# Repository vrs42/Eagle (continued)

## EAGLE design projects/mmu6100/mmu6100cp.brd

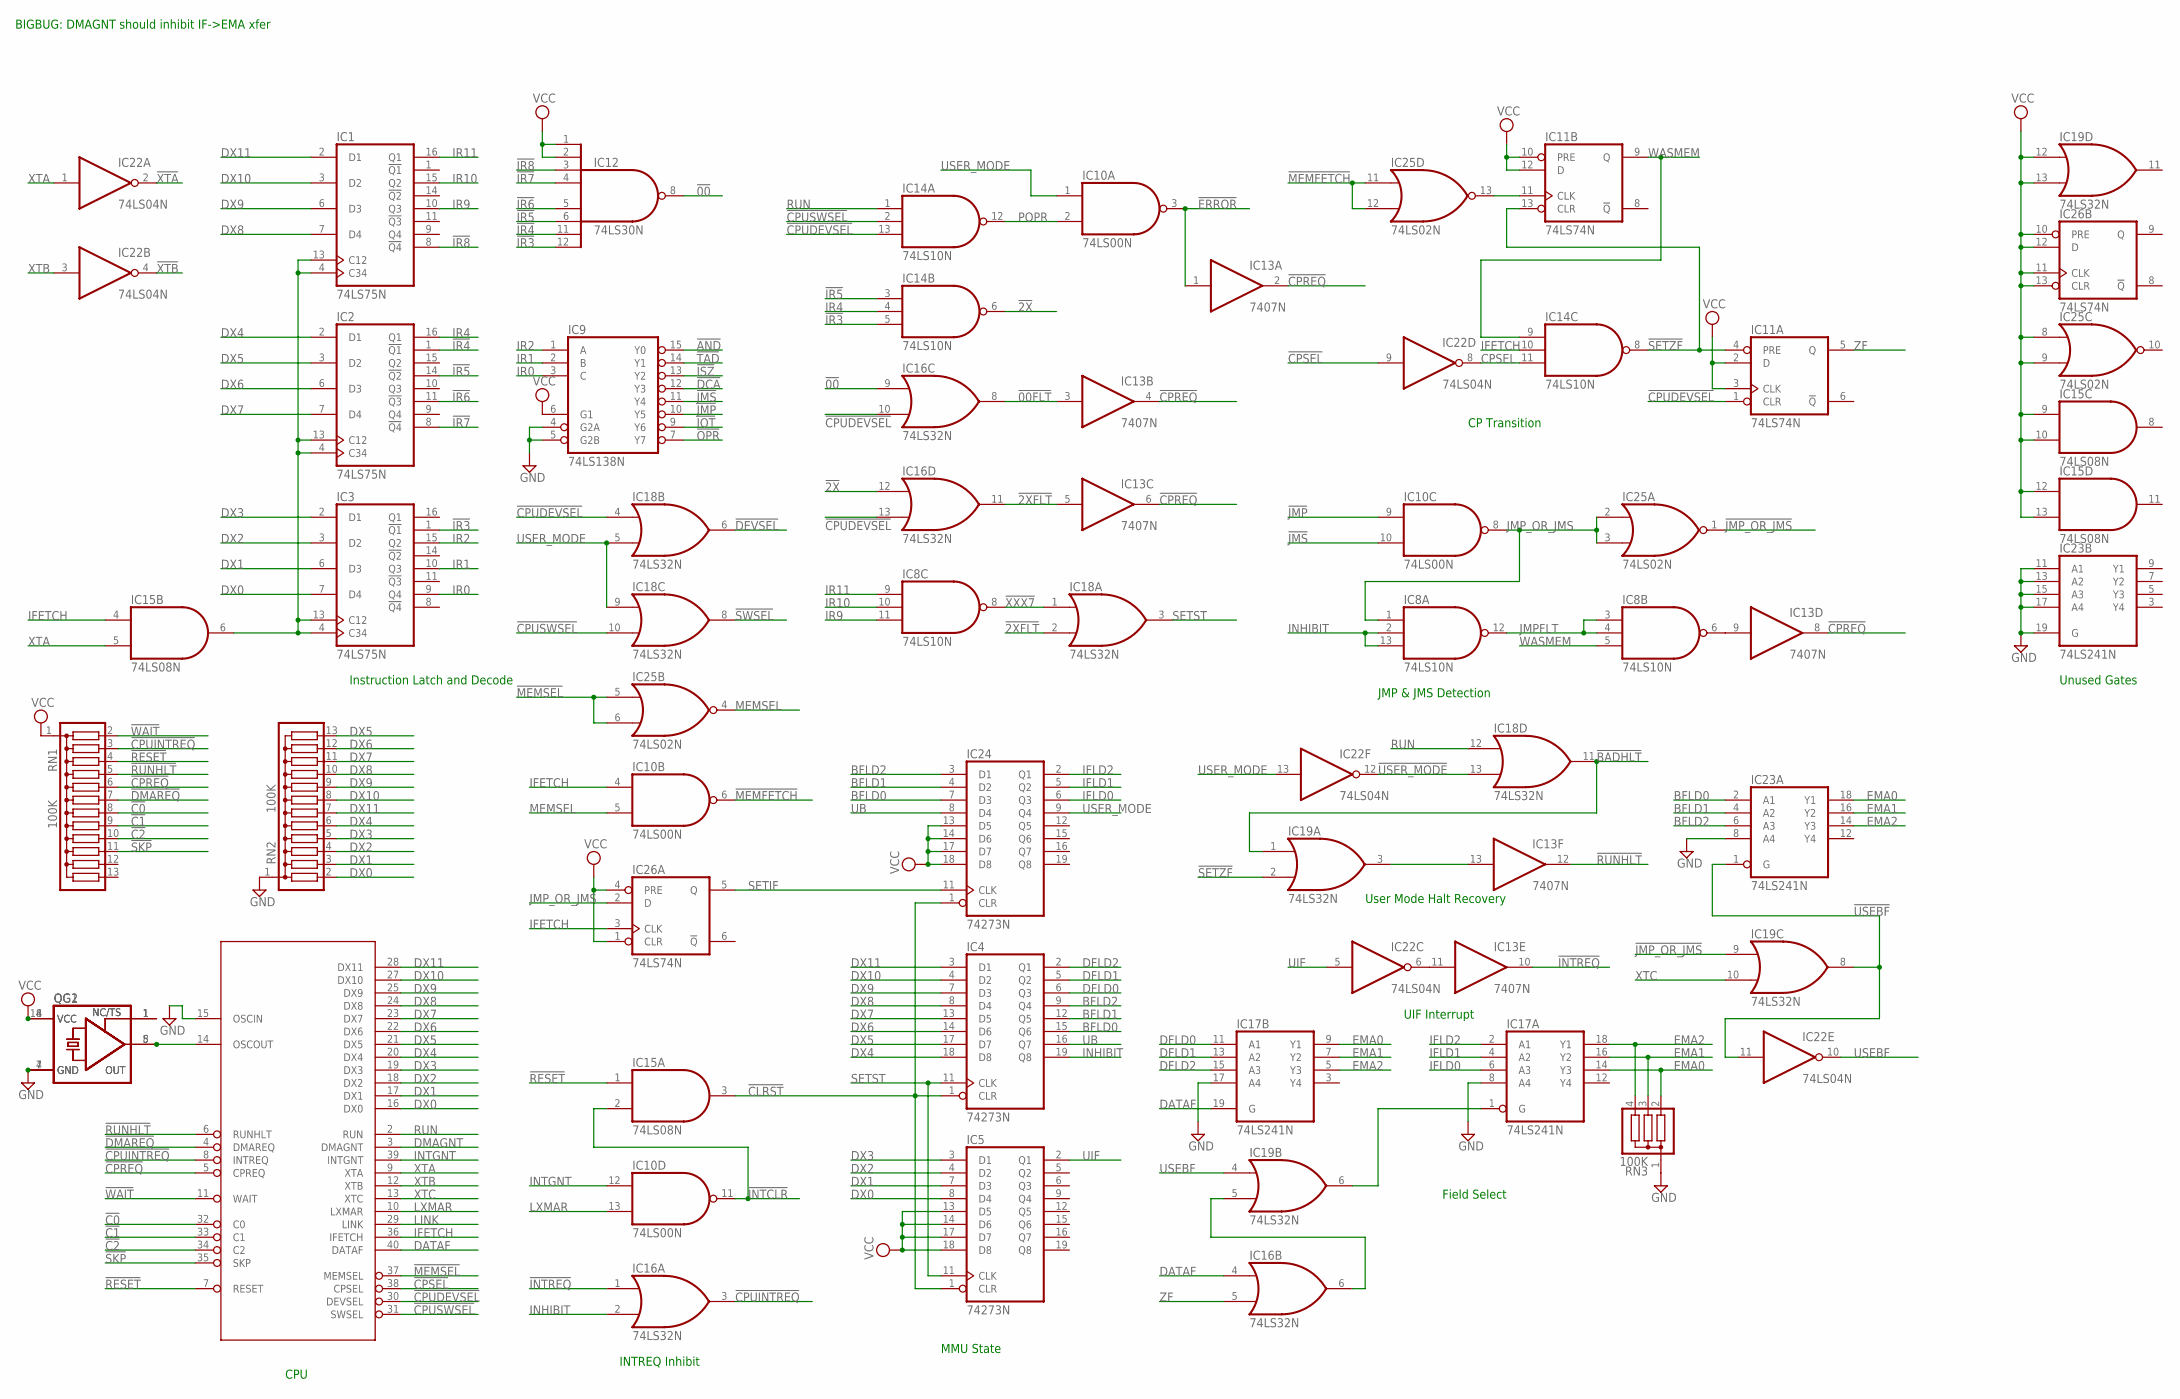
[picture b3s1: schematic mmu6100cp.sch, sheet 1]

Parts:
CPU: IM6100; DIL40
IC1, IC2, IC3: 74LS75N; DIL16
IC4, IC5, IC24: 74273N; DIL20
IC8, IC14: 74LS10N; DIL14
IC9: 74LS138N; DIL16
IC10: 74LS00N; DIL14
IC11, IC26: 74LS74N; DIL14
IC12: 74LS30N; DIL14
IC13: 7407N; DIL14
IC15: 74LS08N; DIL14
IC16, IC18, IC19: 74LS32N; DIL14
IC17, IC23: 74LS241N; DIL20
IC22: 74LS04N; DIL14
IC25: 74LS02N; DIL14
QG1: XO-8; DIL08S
QG2: XO-14; DIL14S
RN1, RN2: 100K; SIL13
RN3: 100K; SIL4

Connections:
!00: IC12.8 (O), IC16.9 (I0)
!00FLT: IC13.3 (I), IC16.8 (O)
!2X: IC14.6 (O), IC16.12 (I0)
!2XFLT: IC13.5 (I), IC16.11 (O), IC18.2 (I1)
!AND: IC9.15 (Y0); also elsewhere on the board
!BADHLT: IC18.11 (O), IC19.1 (I0)
!C0: CPU.32 (C0), RN1.8; also elsewhere on the board
!C1: CPU.33 (C1), RN1.9; also elsewhere on the board
!C2: CPU.34 (C2), RN1.10; also elsewhere on the board
!CLRST: IC4.1 (CLR), IC5.1 (CLR), IC15.3 (O), IC24.1 (CLR)
!CPREQ: CPU.5 (CPREQ), IC13.2 (O), IC13.4 (O), IC13.6 (O), IC13.8 (O), RN1.6; also elsewhere on the board
!CPSEL: CPU.38 (CPSEL), IC22.9 (I)
!CPUDEVSEL: CPU.30 (DEVSEL), IC11.1 (CLR), IC14.13 (I2), IC16.10 (I1), IC16.13 (I1), IC18.4 (I0)
!CPUINTREQ: CPU.8 (INTREQ), IC16.3 (O), RN1.3
!CPUSWSEL: CPU.31 (SWSEL), IC14.2 (I1), IC18.10 (I1)
!DCA: IC9.12 (Y3); also elsewhere on the board
!DEVSEL: IC18.6 (O); also elsewhere on the board
!DMAREQ: CPU.4 (DMAREQ), RN1.7; also elsewhere on the board
!ERROR: IC10.3 (O), IC13.1 (I)
!INTCLR: IC10.11 (O), IC15.2 (I1)
!INTREQ: IC13.10 (O), IC16.1 (I0); also elsewhere on the board
!IOT: IC9.9 (Y6); also elsewhere on the board
!IR3: IC3.1 (!Q1), IC12.12 (I7), IC14.5 (I2)
!IR4: IC2.1 (!Q1), IC12.11 (I6)
!IR5: IC2.14 (!Q2), IC12.6 (I5), IC14.3 (I0)
!IR6: IC2.11 (!Q3), IC12.5 (I4)
!IR7: IC2.8 (!Q4), IC12.4 (I3)
!IR8: IC1.8 (!Q4), IC12.3 (I2)
!ISZ: IC9.13 (Y2); also elsewhere on the board
!JMP: IC9.10 (Y5), IC10.9 (I0)
!JMP_OR_JMS: IC19.9 (I0), IC25.1 (O)
!JMS: IC9.11 (Y4), IC10.10 (I1)
!MEMFETCH: IC10.6 (O), IC25.11 (I0), IC25.12 (I1)
!MEMSEL: CPU.37 (MEMSEL), IC25.5 (I0), IC25.6 (I1); also elsewhere on the board
!OPR: IC9.7 (Y7); also elsewhere on the board
!RESET: CPU.7 (RESET), IC15.1 (I0), RN1.4; also elsewhere on the board
!RUNHLT: CPU.6 (RUNHLT), IC13.12 (O), RN1.5; also elsewhere on the board
!SETZF: IC11.4 (PRE), IC11.13 (CLR), IC14.8 (O), IC19.2 (I1)
!SKP: CPU.35 (SKP), RN1.11; also elsewhere on the board
!SWSEL: IC18.8 (O); also elsewhere on the board
!TAD: IC9.14 (Y1); also elsewhere on the board
!USEBF: IC19.8 (O), IC22.11 (I), IC23.1 (G)
!USER_MODE: IC18.13 (I1), IC22.12 (O)
!WAIT: CPU.11 (WAIT), RN1.2; also elsewhere on the board
!XTA: IC22.2 (O)
!XTB: IC22.4 (O)
!XXX7: IC8.8 (O), IC18.1 (I0)
BFLD0: IC4.15 (Q6), IC23.2 (A1), IC24.7 (D3)
BFLD1: IC4.12 (Q5), IC23.4 (A2), IC24.4 (D2)
BFLD2: IC4.9 (Q4), IC23.6 (A3), IC24.3 (D1)
CPSEL: IC14.11 (I2), IC22.8 (O); also elsewhere on the board
DATAF: CPU.40 (DATAF), IC16.4 (I0), IC17.19 (G)
DFLD0: IC4.6 (Q3), IC17.11 (A1)
DFLD1: IC4.5 (Q2), IC17.13 (A2)
DFLD2: IC4.2 (Q1), IC17.15 (A3)
DMAGNT: CPU.3 (DMAGNT); also elsewhere on the board
DX0: CPU.16 (DX0), IC3.7 (D4), IC5.8 (D4), RN2.2; also elsewhere on the board
DX1: CPU.17 (DX1), IC3.6 (D3), IC5.7 (D3), RN2.3; also elsewhere on the board
DX2: CPU.18 (DX2), IC3.3 (D2), IC5.4 (D2), RN2.4; also elsewhere on the board
DX3: CPU.19 (DX3), IC3.2 (D1), IC5.3 (D1), RN2.5; also elsewhere on the board
DX4: CPU.20 (DX4), IC2.2 (D1), IC4.18 (D8), RN2.6; also elsewhere on the board
DX5: CPU.21 (DX5), IC2.3 (D2), IC4.17 (D7), RN2.13; also elsewhere on the board
DX6: CPU.22 (DX6), IC2.6 (D3), IC4.14 (D6), RN2.12; also elsewhere on the board
DX7: CPU.23 (DX7), IC2.7 (D4), IC4.13 (D5), RN2.11; also elsewhere on the board
DX8: CPU.24 (DX8), IC1.7 (D4), IC4.8 (D4), RN2.10; also elsewhere on the board
DX9: CPU.25 (DX9), IC1.6 (D3), IC4.7 (D3), RN2.9; also elsewhere on the board
DX10: CPU.27 (DX10), IC1.3 (D2), IC4.4 (D2), RN2.8; also elsewhere on the board
DX11: CPU.28 (DX11), IC1.2 (D1), IC4.3 (D1), RN2.7; also elsewhere on the board
EMA0: IC17.9 (Y1), IC17.14 (Y3), IC23.18 (Y1), RN3.2; also elsewhere on the board
EMA1: IC17.7 (Y2), IC17.16 (Y2), IC23.16 (Y2), RN3.3; also elsewhere on the board
EMA2: IC17.5 (Y3), IC17.18 (Y1), IC23.14 (Y3), RN3.4; also elsewhere on the board
GND: CPU.15 (OSCIN), CPU.26 (GND), IC1.12 (GND), IC2.12 (GND), IC3.12 (GND), IC4.10 (GND), IC5.10 (GND), IC8.7 (GND), IC9.4 (G2A), IC9.5 (G2B), IC9.8 (GND), IC10.7 (GND), IC11.7 (GND), IC12.7 (GND), IC13.7 (GND), IC14.7 (GND), IC15.7 (GND), IC16.7 (GND), IC17.8 (A4), IC17.10 (GND), IC17.17 (A4), IC18.7 (GND), IC19.7 (GND), IC22.7 (GND), IC23.8 (A4), IC23.10 (GND), IC23.11 (A1), IC23.13 (A2), IC23.15 (A3), IC23.17 (A4), IC23.19 (G), IC24.10 (GND), IC25.7 (GND), IC26.7 (GND), QG1.4 (GND), QG2.7 (GND), RN2.1, RN3.1; also elsewhere on the board
IFETCH: CPU.36 (IFETCH), IC10.4 (I0), IC14.10 (I1), IC15.4 (I0), IC26.3 (CLK)
IFLD0: IC17.6 (A3), IC24.6 (Q3)
IFLD1: IC17.4 (A2), IC24.5 (Q2)
IFLD2: IC17.2 (A1), IC24.2 (Q1)
INHIBIT: IC4.19 (Q8), IC8.2 (I1), IC8.13 (I2), IC16.2 (I1)
INTGNT: CPU.39 (INTGNT), IC10.12 (I0); also elsewhere on the board
IR0: IC3.9 (Q4), IC9.3 (C)
IR1: IC3.10 (Q3), IC9.2 (B)
IR2: IC3.15 (Q2), IC9.1 (A)
IR4: IC2.16 (Q1), IC14.4 (I1)
IR9: IC1.10 (Q3), IC8.11 (I2)
IR10: IC1.15 (Q2), IC8.10 (I1)
IR11: IC1.16 (Q1), IC8.9 (I0)
JMPFLT: IC8.3 (I0), IC8.4 (I1), IC8.12 (O)
JMP_OR_JMS: IC8.1 (I0), IC10.8 (O), IC25.2 (I0), IC25.3 (I1), IC26.2 (D)
LINK: CPU.29 (LINK); also elsewhere on the board
LXMAR: CPU.10 (LXMAR), IC10.13 (I1); also elsewhere on the board
MEMSEL: IC10.5 (I1), IC25.4 (O); also elsewhere on the board
unnamed: QG1.1 (TS), QG2.1 (TS)
unnamed: IC1.4 (C34), IC1.13 (C12), IC2.4 (C34), IC2.13 (C12), IC3.4 (C34), IC3.13 (C12), IC15.6 (O)
unnamed: IC13.11 (I), IC22.6 (O)
unnamed: IC11.11 (CLK), IC25.13 (O)
unnamed: IC13.13 (I), IC19.3 (O)
unnamed: IC16.6 (O), IC19.5 (I1)
unnamed: IC17.1 (G), IC19.6 (O)
unnamed: IC8.6 (O), IC13.9 (I)
OSCOUT: CPU.14 (OSCOUT), QG1.5 (OUT), QG2.8 (OUT)
POPR: IC10.2 (I1), IC14.12 (O)
RUN: CPU.2 (RUN), IC14.1 (I0), IC18.12 (I0)
SETIF: IC24.11 (CLK), IC26.5 (Q)
SETST: IC4.11 (CLK), IC5.11 (CLK), IC18.3 (O)
UB: IC4.16 (Q7), IC24.8 (D4)
UIF: IC5.2 (Q1), IC22.5 (I)
USEBF: IC19.4 (I0), IC22.10 (O)
USER_MODE: IC10.1 (I0), IC18.5 (I1), IC18.9 (I0), IC22.13 (I), IC24.9 (Q4)
VCC: CPU.1 (VCC), IC1.5 (VCC), IC2.5 (VCC), IC3.5 (VCC), IC4.20 (VCC), IC5.13 (D5), IC5.14 (D6), IC5.17 (D7), IC5.18 (D8), IC5.20 (VCC), IC8.14 (VCC), IC9.6 (G1), IC9.16 (VCC), IC10.14 (VCC), IC11.2 (D), IC11.3 (CLK), IC11.10 (PRE), IC11.12 (D), IC11.14 (VCC), IC12.1 (I0), IC12.2 (I1), IC12.14 (VCC), IC13.14 (VCC), IC14.14 (VCC), IC15.9 (I0), IC15.10 (I1), IC15.12 (I0), IC15.13 (I1), IC15.14 (VCC), IC16.14 (VCC), IC17.20 (VCC), IC18.14 (VCC), IC19.12 (I0), IC19.13 (I1), IC19.14 (VCC), IC22.14 (VCC), IC23.20 (VCC), IC24.13 (D5), IC24.14 (D6), IC24.17 (D7), IC24.18 (D8), IC24.20 (VCC), IC25.8 (I0), IC25.9 (I1), IC25.14 (VCC), IC26.1 (CLR), IC26.4 (PRE), IC26.10 (PRE), IC26.11 (CLK), IC26.12 (D), IC26.13 (CLR), IC26.14 (VCC), QG1.8 (VCC), QG2.14 (VCC), RN1.1; also elsewhere on the board
WASMEM: IC8.5 (I2), IC11.9 (Q), IC14.9 (I0)
XTA: CPU.9 (XTA), IC15.5 (I1), IC22.1 (I); also elsewhere on the board
XTB: CPU.12 (XTB), IC22.3 (I); also elsewhere on the board
XTC: CPU.13 (XTC), IC19.10 (I1); also elsewhere on the board
ZF: IC11.5 (Q), IC16.5 (I1)

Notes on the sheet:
Instruction Latch and Decode
CPU
Field Select
INTREQ Inhibit
JMP & JMS Detection
CP Transition
MMU State
Unused Gates
User Mode Halt Recovery
UIF Interrupt
BIGBUG: DMAGNT should inhibit IF->EMA xfer

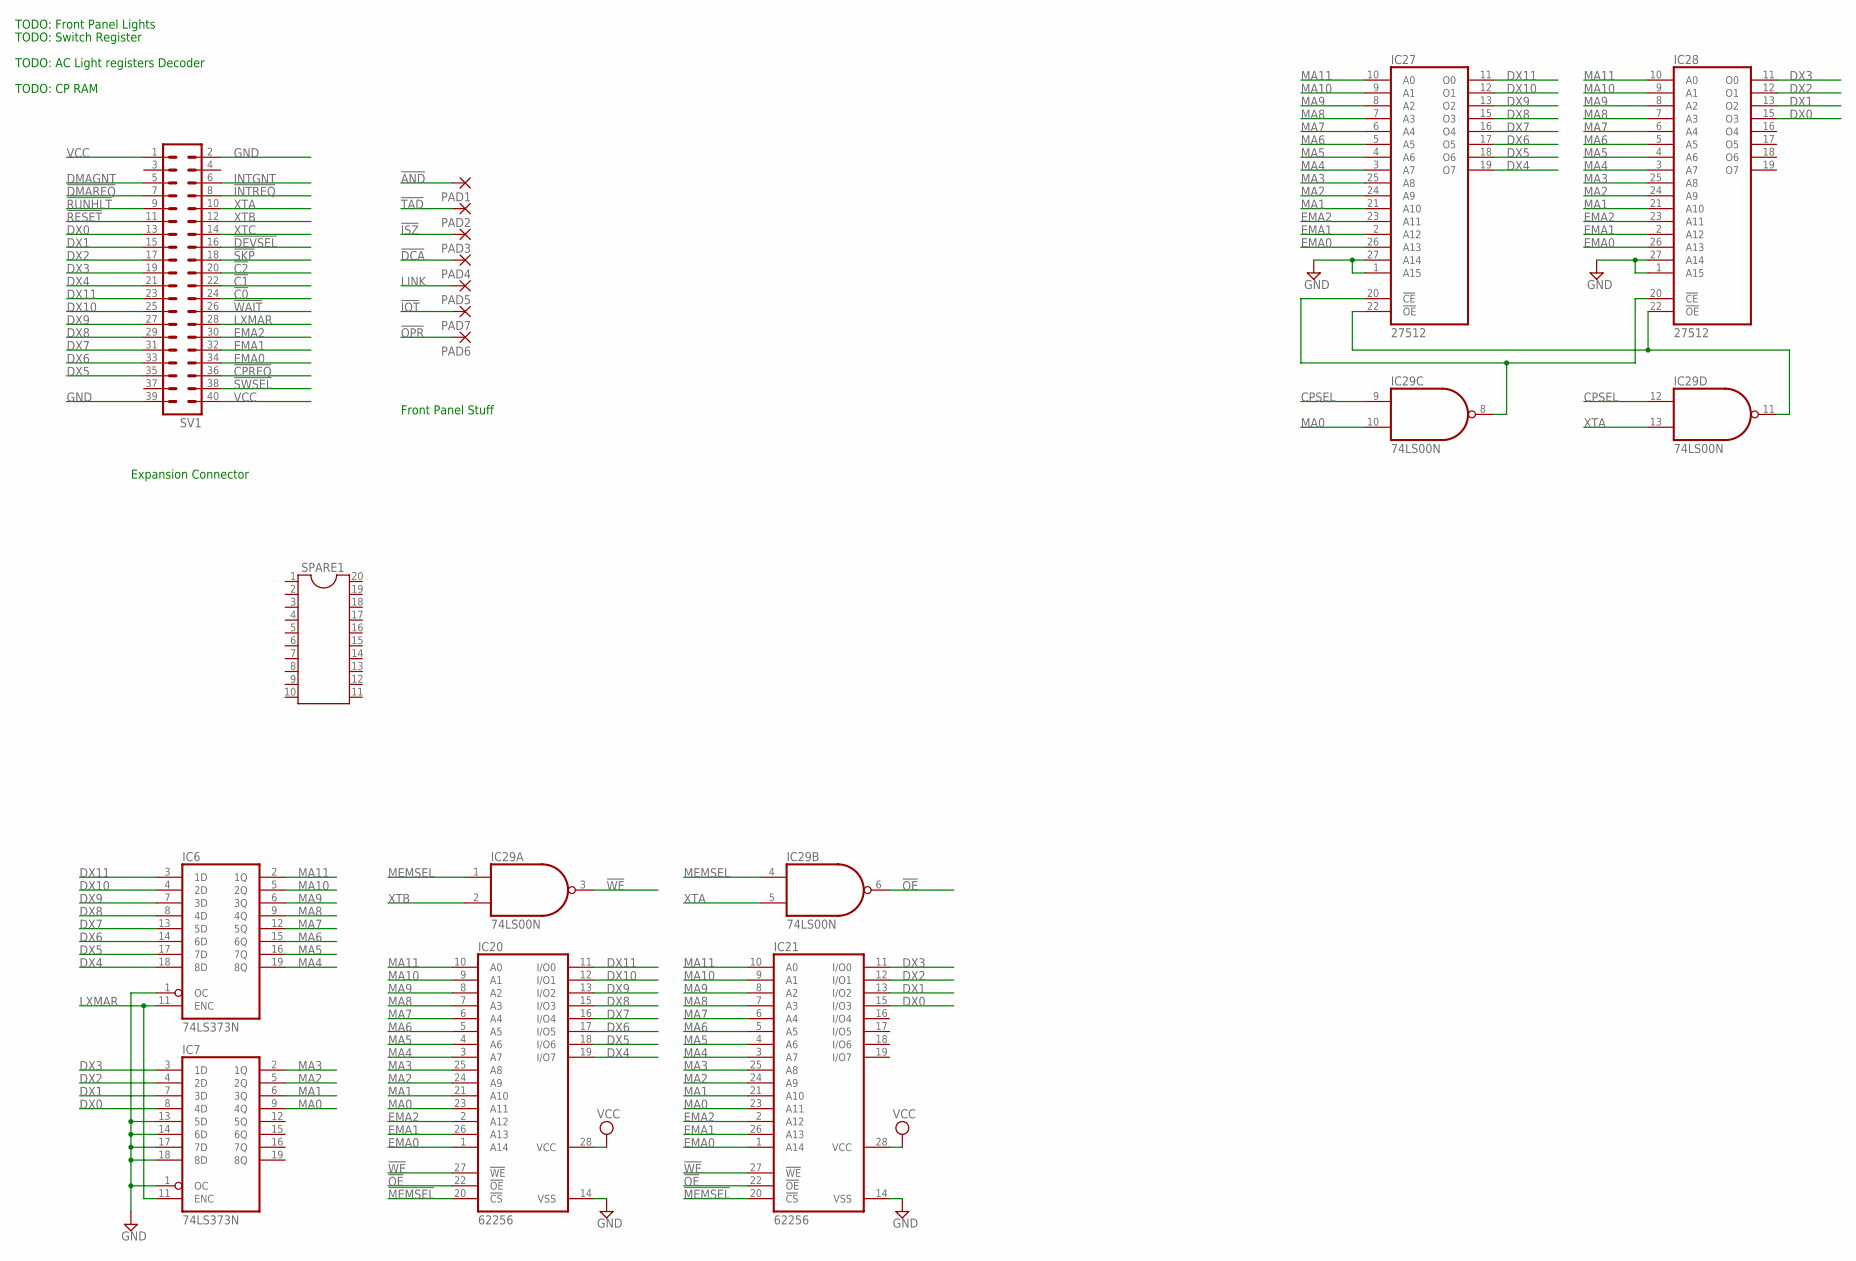
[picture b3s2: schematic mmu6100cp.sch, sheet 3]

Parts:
IC6, IC7: 74LS373N; DIL20
IC20, IC21: 62256; DIL28-6
IC27, IC28: 27512; DIL28
IC29: 74LS00N; DIL14
PAD1, PAD2, PAD3, PAD4, PAD5, PAD6, PAD7: 2,15/1,0
SPARE1: DIL20
SV1: MA20-2

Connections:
!AND: PAD1.1; also elsewhere on the board
!C0: SV1.24; also elsewhere on the board
!C1: SV1.22; also elsewhere on the board
!C2: SV1.20; also elsewhere on the board
!CPREQ: SV1.36; also elsewhere on the board
!DCA: PAD4.1; also elsewhere on the board
!DEVSEL: SV1.16; also elsewhere on the board
!DMAREQ: SV1.7; also elsewhere on the board
!INTREQ: SV1.8; also elsewhere on the board
!IOT: PAD7.1; also elsewhere on the board
!ISZ: PAD3.1; also elsewhere on the board
!MEMSEL: IC20.20 (!CS), IC21.20 (!CS); also elsewhere on the board
!OE: IC20.22 (!OE), IC21.22 (!OE), IC29.6 (O)
!OPR: PAD6.1; also elsewhere on the board
!RESET: SV1.11; also elsewhere on the board
!RUNHLT: SV1.9; also elsewhere on the board
!SKP: SV1.18; also elsewhere on the board
!SWSEL: SV1.38; also elsewhere on the board
!TAD: PAD2.1; also elsewhere on the board
!WAIT: SV1.26; also elsewhere on the board
!WE: IC20.27 (!WE), IC21.27 (!WE), IC29.3 (O)
CPSEL: IC29.9 (I0), IC29.12 (I0); also elsewhere on the board
DMAGNT: SV1.5; also elsewhere on the board
DX0: IC7.8 (4D), IC21.15 (I/O3), IC28.15 (O3), SV1.13; also elsewhere on the board
DX1: IC7.7 (3D), IC21.13 (I/O2), IC28.13 (O2), SV1.15; also elsewhere on the board
DX2: IC7.4 (2D), IC21.12 (I/O1), IC28.12 (O1), SV1.17; also elsewhere on the board
DX3: IC7.3 (1D), IC21.11 (I/O0), IC28.11 (O0), SV1.19; also elsewhere on the board
DX4: IC6.18 (8D), IC20.19 (I/O7), IC27.19 (O7), SV1.21; also elsewhere on the board
DX5: IC6.17 (7D), IC20.18 (I/O6), IC27.18 (O6), SV1.35; also elsewhere on the board
DX6: IC6.14 (6D), IC20.17 (I/O5), IC27.17 (O5), SV1.33; also elsewhere on the board
DX7: IC6.13 (5D), IC20.16 (I/O4), IC27.16 (O4), SV1.31; also elsewhere on the board
DX8: IC6.8 (4D), IC20.15 (I/O3), IC27.15 (O3), SV1.29; also elsewhere on the board
DX9: IC6.7 (3D), IC20.13 (I/O2), IC27.13 (O2), SV1.27; also elsewhere on the board
DX10: IC6.4 (2D), IC20.12 (I/O1), IC27.12 (O1), SV1.25; also elsewhere on the board
DX11: IC6.3 (1D), IC20.11 (I/O0), IC27.11 (O0), SV1.23; also elsewhere on the board
EMA0: IC20.1 (A14), IC21.1 (A14), IC27.26 (A13), IC28.26 (A13), SV1.34; also elsewhere on the board
EMA1: IC20.26 (A13), IC21.26 (A13), IC27.2 (A12), IC28.2 (A12), SV1.32; also elsewhere on the board
EMA2: IC20.2 (A12), IC21.2 (A12), IC27.23 (A11), IC28.23 (A11), SV1.30; also elsewhere on the board
GND: IC6.1 (OC), IC6.10 (GND), IC7.1 (OC), IC7.10 (GND), IC7.13 (5D), IC7.14 (6D), IC7.17 (7D), IC7.18 (8D), IC20.14 (VSS), IC21.14 (VSS), IC27.1 (A15), IC27.14 (GND), IC27.27 (A14), IC28.1 (A15), IC28.14 (GND), IC28.27 (A14), IC29.7 (GND), SV1.2, SV1.39; also elsewhere on the board
INTGNT: SV1.6; also elsewhere on the board
LINK: PAD5.1; also elsewhere on the board
LXMAR: IC6.11 (ENC), IC7.11 (ENC), SV1.28; also elsewhere on the board
MA0: IC7.9 (4Q), IC20.23 (A11), IC21.23 (A11), IC29.10 (I1)
MA1: IC7.6 (3Q), IC20.21 (A10), IC21.21 (A10), IC27.21 (A10), IC28.21 (A10)
MA2: IC7.5 (2Q), IC20.24 (A9), IC21.24 (A9), IC27.24 (A9), IC28.24 (A9)
MA3: IC7.2 (1Q), IC20.25 (A8), IC21.25 (A8), IC27.25 (A8), IC28.25 (A8)
MA4: IC6.19 (8Q), IC20.3 (A7), IC21.3 (A7), IC27.3 (A7), IC28.3 (A7)
MA5: IC6.16 (7Q), IC20.4 (A6), IC21.4 (A6), IC27.4 (A6), IC28.4 (A6)
MA6: IC6.15 (6Q), IC20.5 (A5), IC21.5 (A5), IC27.5 (A5), IC28.5 (A5)
MA7: IC6.12 (5Q), IC20.6 (A4), IC21.6 (A4), IC27.6 (A4), IC28.6 (A4)
MA8: IC6.9 (4Q), IC20.7 (A3), IC21.7 (A3), IC27.7 (A3), IC28.7 (A3)
MA9: IC6.6 (3Q), IC20.8 (A2), IC21.8 (A2), IC27.8 (A2), IC28.8 (A2)
MA10: IC6.5 (2Q), IC20.9 (A1), IC21.9 (A1), IC27.9 (A1), IC28.9 (A1)
MA11: IC6.2 (1Q), IC20.10 (A0), IC21.10 (A0), IC27.10 (A0), IC28.10 (A0)
MEMSEL: IC29.1 (I0), IC29.4 (I0); also elsewhere on the board
unnamed: IC27.20 (!CE), IC28.20 (!CE), IC29.8 (O)
unnamed: IC27.22 (!OE), IC28.22 (!OE), IC29.11 (O)
VCC: IC6.20 (VCC), IC7.20 (VCC), IC20.28 (VCC), IC21.28 (VCC), IC27.28 (VCC), IC28.28 (VCC), IC29.14 (VCC), SV1.1, SV1.40; also elsewhere on the board
XTA: IC29.5 (I1), IC29.13 (I1), SV1.10; also elsewhere on the board
XTB: IC29.2 (I1), SV1.12; also elsewhere on the board
XTC: SV1.14; also elsewhere on the board

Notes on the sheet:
Expansion Connector
Front Panel Stuff
TODO: Front Panel Lights
TODO: Switch Register
TODO: AC Light registers Decoder
TODO: CP RAM

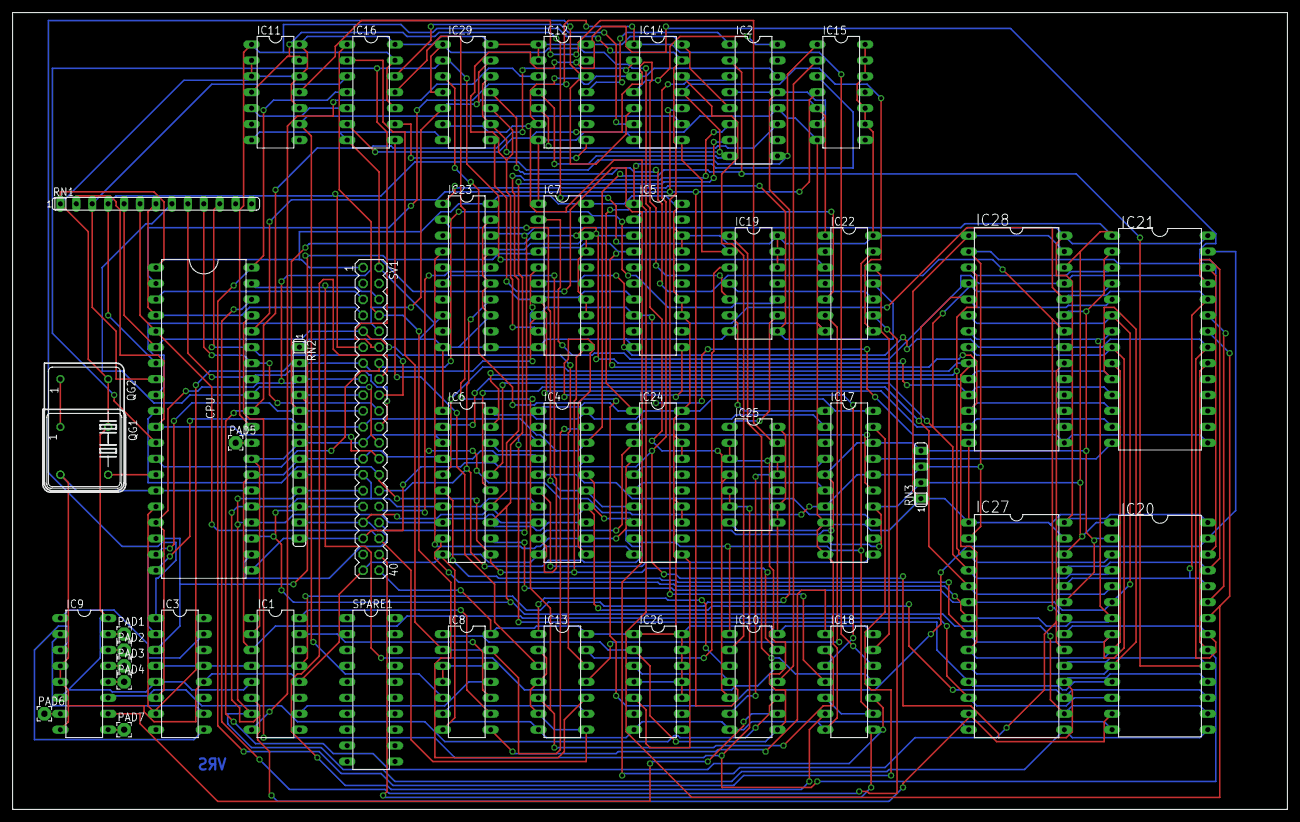
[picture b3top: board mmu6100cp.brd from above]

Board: 2 copper layers, 203.2 x 127.0 mm, 44 parts (0 on the bottom side), 127 nets.

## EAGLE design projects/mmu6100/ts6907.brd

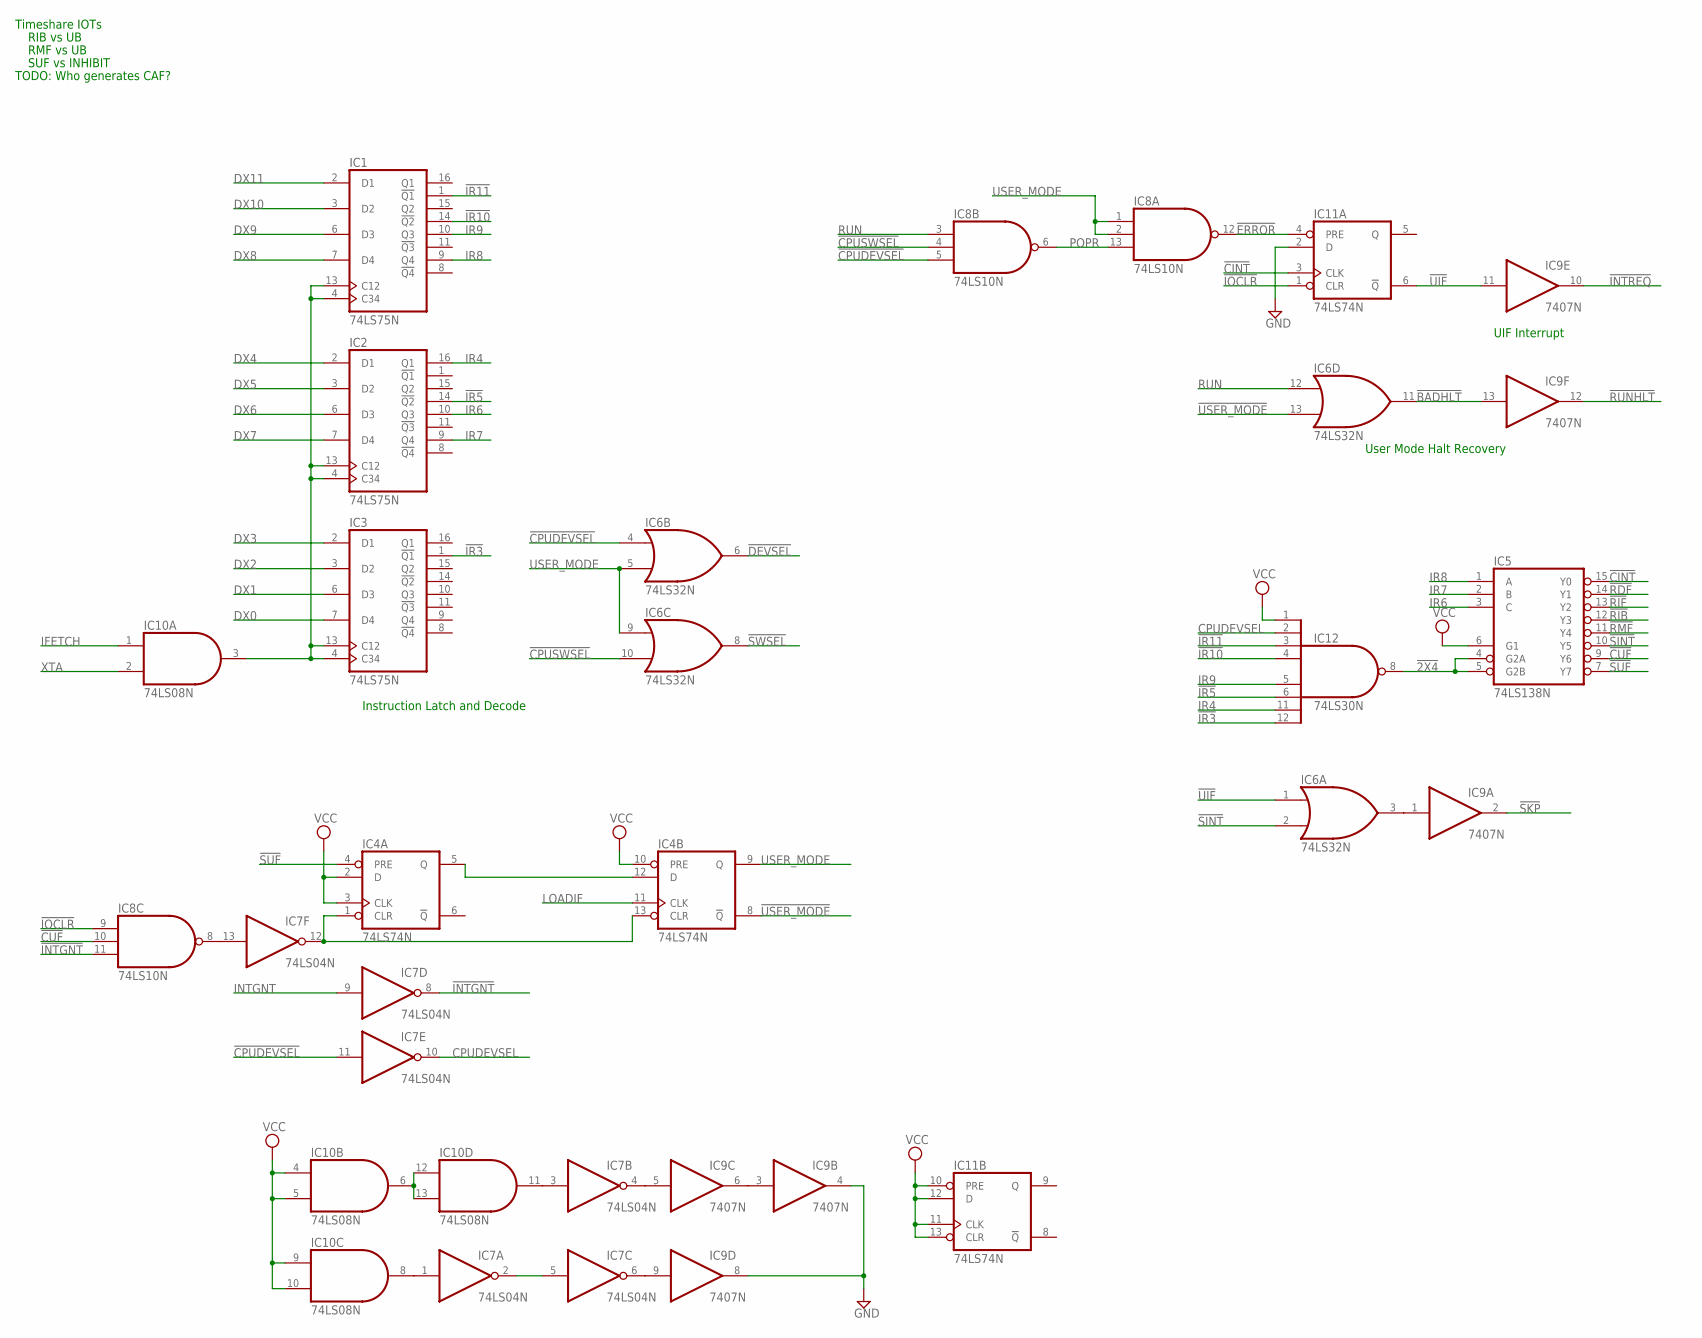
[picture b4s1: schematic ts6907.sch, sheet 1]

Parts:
IC1, IC2, IC3: 74LS75N; DIL16
IC4, IC11: 74LS74N; DIL14
IC5: 74LS138N; DIL16
IC6: 74LS32N; DIL14
IC7: 74LS04N; DIL14
IC8: 74LS10N; DIL14
IC9: 7407N; DIL14
IC10: 74LS08N; DIL14
IC12: 74LS30N; DIL14

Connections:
!2X4: IC5.4 (G2A), IC5.5 (G2B), IC12.8 (O)
!BADHLT: IC6.11 (O), IC9.13 (I)
!CINT: IC5.15 (Y0), IC11.3 (CLK)
!CPUDEVSEL: IC6.4 (I0), IC7.11 (I), IC8.5 (I2); also elsewhere on the board
!CPUSWSEL: IC6.10 (I1), IC8.4 (I1); also elsewhere on the board
!CUF: IC5.9 (Y6), IC8.10 (I1)
!DEVSEL: IC6.6 (O); also elsewhere on the board
!ERROR: IC8.12 (O), IC11.4 (PRE)
!INTGNT: IC7.8 (O), IC8.11 (I2)
!INTREQ: IC9.10 (O); also elsewhere on the board
!IOCLR: IC8.9 (I0), IC11.1 (CLR); also elsewhere on the board
!IR3: IC3.1 (!Q1), IC12.12 (I7)
!IR5: IC2.14 (!Q2), IC12.6 (I5)
!IR10: IC1.14 (!Q2), IC12.4 (I3)
!IR11: IC1.1 (!Q1), IC12.3 (I2)
!RDF: IC5.14 (Y1)
!RIB: IC5.12 (Y3)
!RIF: IC5.13 (Y2)
!RMF: IC5.11 (Y4)
!RUNHLT: IC9.12 (O); also elsewhere on the board
!SINT: IC5.10 (Y5), IC6.2 (I1)
!SKP: IC9.2 (O); also elsewhere on the board
!SUF: IC4.4 (PRE), IC5.7 (Y7)
!SWSEL: IC6.8 (O); also elsewhere on the board
!UIF: IC6.1 (I0), IC9.11 (I), IC11.6 (!Q)
!USER_MODE: IC4.8 (!Q), IC6.13 (I1)
CPUDEVSEL: IC7.10 (O), IC12.2 (I1)
DX0: IC3.7 (D4); also elsewhere on the board
DX1: IC3.6 (D3); also elsewhere on the board
DX2: IC3.3 (D2); also elsewhere on the board
DX3: IC3.2 (D1); also elsewhere on the board
DX4: IC2.2 (D1); also elsewhere on the board
DX5: IC2.3 (D2); also elsewhere on the board
DX6: IC2.6 (D3); also elsewhere on the board
DX7: IC2.7 (D4); also elsewhere on the board
DX8: IC1.7 (D4); also elsewhere on the board
DX9: IC1.6 (D3); also elsewhere on the board
DX10: IC1.3 (D2); also elsewhere on the board
DX11: IC1.2 (D1); also elsewhere on the board
GND: IC1.12 (GND), IC2.12 (GND), IC3.12 (GND), IC4.7 (GND), IC5.8 (GND), IC6.7 (GND), IC7.7 (GND), IC8.7 (GND), IC9.4 (O), IC9.7 (GND), IC9.8 (O), IC10.7 (GND), IC11.2 (D), IC11.7 (GND), IC12.7 (GND); also elsewhere on the board
IFETCH: IC10.1 (I0); also elsewhere on the board
INTGNT: IC7.9 (I); also elsewhere on the board
IR4: IC2.16 (Q1), IC12.11 (I6)
IR6: IC2.10 (Q3), IC5.3 (C)
IR7: IC2.9 (Q4), IC5.2 (B)
IR8: IC1.9 (Q4), IC5.1 (A)
IR9: IC1.10 (Q3), IC12.5 (I4)
LOADIF: IC4.11 (CLK); also elsewhere on the board
unnamed: IC4.5 (Q), IC4.12 (D)
unnamed: IC7.1 (I), IC10.8 (O)
unnamed: IC1.4 (C34), IC1.13 (C12), IC2.4 (C34), IC2.13 (C12), IC3.4 (C34), IC3.13 (C12), IC10.3 (O)
unnamed: IC4.1 (CLR), IC4.13 (CLR), IC7.12 (O)
unnamed: IC7.3 (I), IC10.11 (O)
unnamed: IC7.2 (O), IC7.5 (I)
unnamed: IC10.6 (O), IC10.12 (I0), IC10.13 (I1)
unnamed: IC7.4 (O), IC9.5 (I)
unnamed: IC7.6 (O), IC9.9 (I)
unnamed: IC9.3 (I), IC9.6 (O)
unnamed: IC6.3 (O), IC9.1 (I)
unnamed: IC7.13 (I), IC8.8 (O)
POPR: IC8.6 (O), IC8.13 (I2)
RUN: IC6.12 (I0), IC8.3 (I0); also elsewhere on the board
USER_MODE: IC4.9 (Q), IC6.5 (I1), IC6.9 (I0), IC8.1 (I0), IC8.2 (I1)
VCC: IC1.5 (VCC), IC2.5 (VCC), IC3.5 (VCC), IC4.2 (D), IC4.3 (CLK), IC4.10 (PRE), IC4.14 (VCC), IC5.6 (G1), IC5.16 (VCC), IC6.14 (VCC), IC7.14 (VCC), IC8.14 (VCC), IC9.14 (VCC), IC10.4 (I0), IC10.5 (I1), IC10.9 (I0), IC10.10 (I1), IC10.14 (VCC), IC11.10 (PRE), IC11.11 (CLK), IC11.12 (D), IC11.13 (CLR), IC11.14 (VCC), IC12.1 (I0), IC12.14 (VCC); also elsewhere on the board
XTA: IC10.2 (I1); also elsewhere on the board

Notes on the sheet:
Instruction Latch and Decode
User Mode Halt Recovery
UIF Interrupt
TODO: Who generates CAF?
Timeshare IOTs
RIB vs UB
RMF vs UB
SUF vs INHIBIT

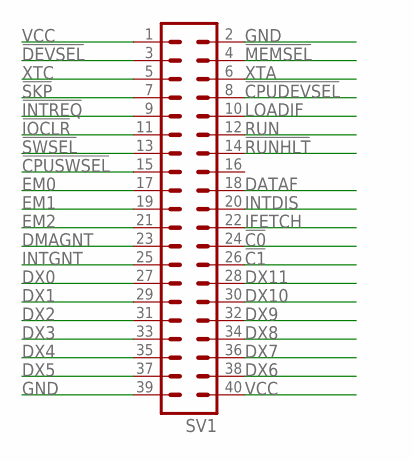
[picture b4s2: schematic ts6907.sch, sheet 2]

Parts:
SV1: MA20-2

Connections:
!C0: SV1.24
!C1: SV1.26
!CPUDEVSEL: SV1.8; also elsewhere on the board
!CPUSWSEL: SV1.15; also elsewhere on the board
!DEVSEL: SV1.3; also elsewhere on the board
!INTREQ: SV1.9; also elsewhere on the board
!IOCLR: SV1.11; also elsewhere on the board
!MEMSEL: SV1.4
!RUNHLT: SV1.14; also elsewhere on the board
!SKP: SV1.7; also elsewhere on the board
!SWSEL: SV1.13; also elsewhere on the board
DATAF: SV1.18
DMAGNT: SV1.23
DX0: SV1.27; also elsewhere on the board
DX1: SV1.29; also elsewhere on the board
DX2: SV1.31; also elsewhere on the board
DX3: SV1.33; also elsewhere on the board
DX4: SV1.35; also elsewhere on the board
DX5: SV1.37; also elsewhere on the board
DX6: SV1.38; also elsewhere on the board
DX7: SV1.36; also elsewhere on the board
DX8: SV1.34; also elsewhere on the board
DX9: SV1.32; also elsewhere on the board
DX10: SV1.30; also elsewhere on the board
DX11: SV1.28; also elsewhere on the board
EM0: SV1.17
EM1: SV1.19
EM2: SV1.21
GND: SV1.2, SV1.39; also elsewhere on the board
IFETCH: SV1.22; also elsewhere on the board
INTDIS: SV1.20
INTGNT: SV1.25; also elsewhere on the board
LOADIF: SV1.10; also elsewhere on the board
RUN: SV1.12; also elsewhere on the board
VCC: SV1.1, SV1.40; also elsewhere on the board
XTA: SV1.6; also elsewhere on the board
XTC: SV1.5

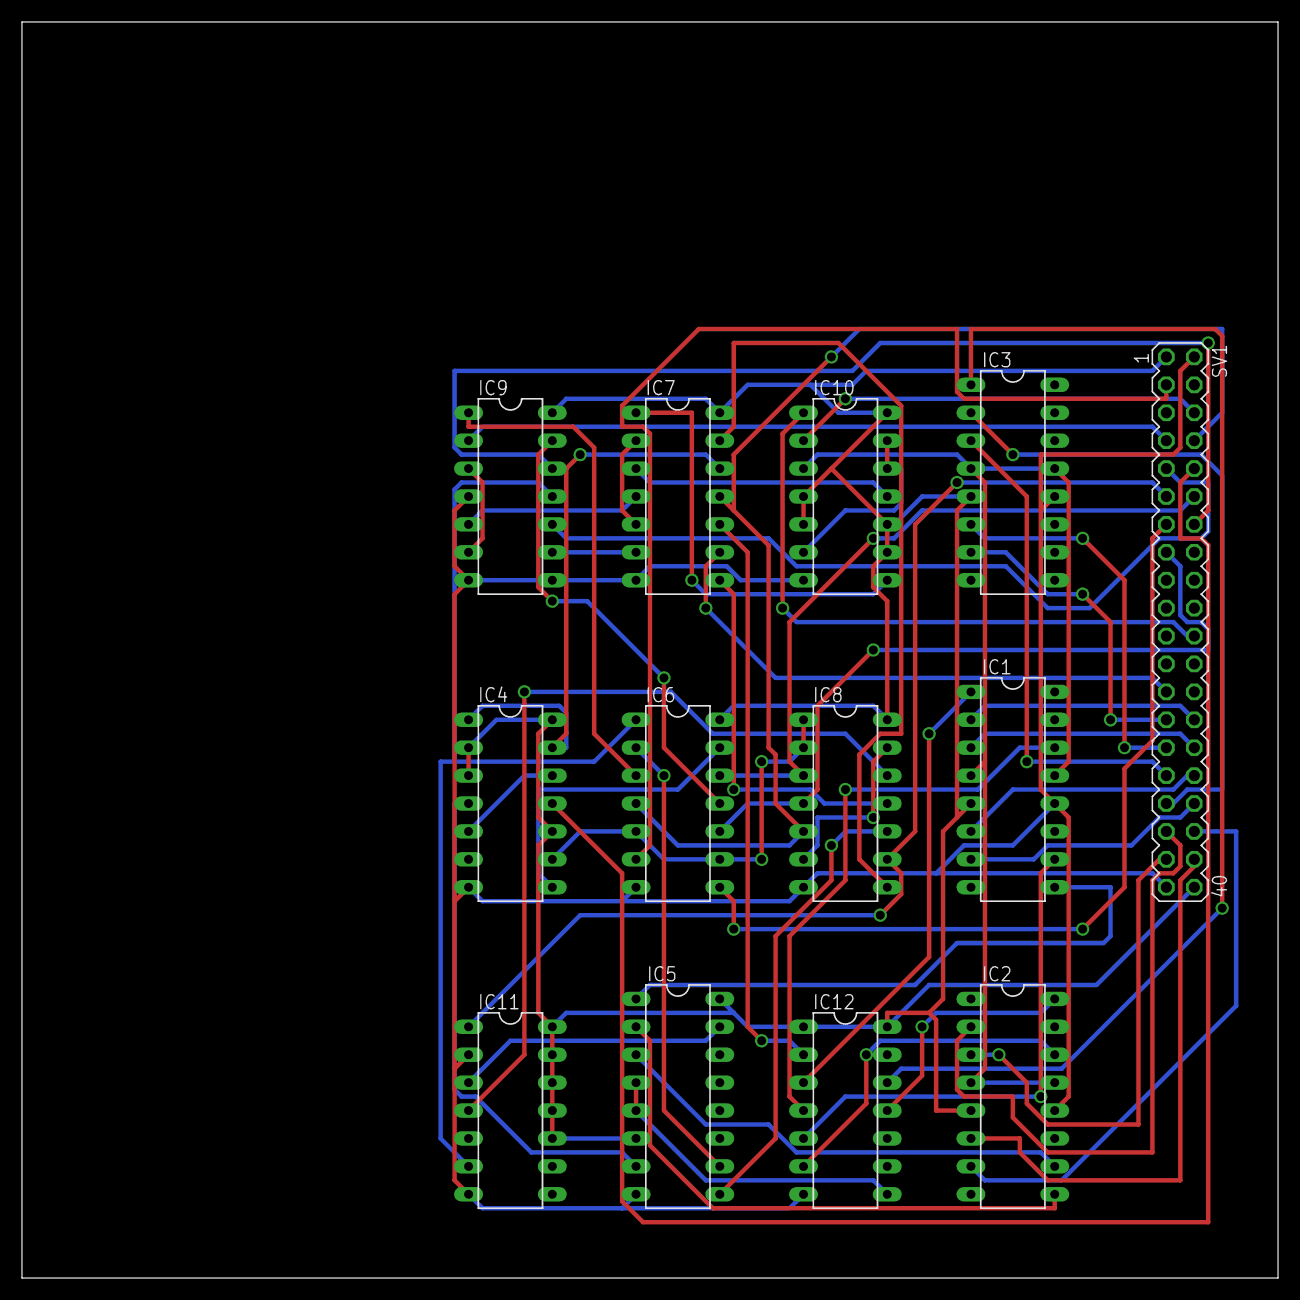
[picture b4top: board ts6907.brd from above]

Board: 2 copper layers, 114.3 x 114.3 mm, 13 parts (0 on the bottom side), 61 nets.
